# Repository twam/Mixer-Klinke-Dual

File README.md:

Mixer-Klinke-Dual
===

This repository is part of the USB audio mixer project described on https://www.twam.info/general/building-a-custom-usb-audio-mixer.

## License

[![CC BY-SA 4.0][cc-by-sa-shield]][cc-by-sa]

This work is licensed under a [Creative Commons Attribution-NonCommercial-ShareAlike 4.0 International License][cc-by-sa].

[![CC BY-SA 4.0][cc-by-sa-image]][cc-by-sa]

[cc-by-sa]: http://creativecommons.org/licenses/by-nc-sa/4.0/
[cc-by-sa-image]: https://licensebuttons.net/l/by-nc-sa/4.0/88x31.png
[cc-by-sa-shield]: https://img.shields.io/badge/License-CC%20BY--NC--SA%204.0-lightgrey.svg

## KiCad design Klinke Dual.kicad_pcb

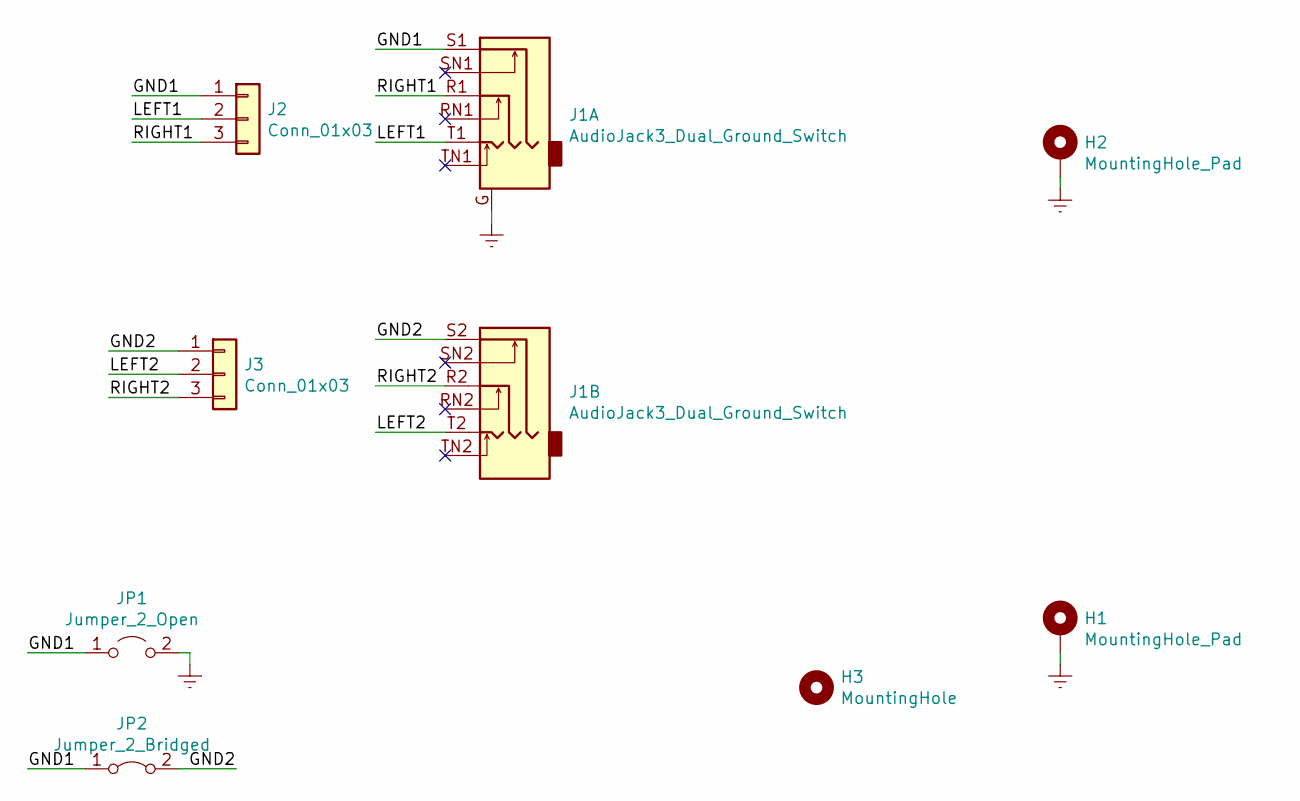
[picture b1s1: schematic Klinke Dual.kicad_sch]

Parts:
H1, H2: MountingHole_Pad; MountingHole_3.2mm_M3_DIN965_Pad
H3: MountingHole; MountingHole_3.2mm_M3_DIN965
J1: AudioJack3_Dual_Ground_Switch; Jack_6.35mm_Neutrik_NSJ12HF-1_Horizontal
J2, J3: Conn_01x03; PinHeader_1x03_P2.54mm_Vertical
JP1: Jumper_2_Open; SolderJumper-2_P1.3mm_Open_RoundedPad1.0x1.5mm
JP2: Jumper_2_Bridged; SolderJumper-2_P1.3mm_Open_RoundedPad1.0x1.5mm

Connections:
/GND1: J1.S1, J2.1, JP1.1 (A), JP2.1 (A)
/GND2: J1.S2, J3.1, JP2.2 (B)
/LEFT1: J1.T1, J2.2
/LEFT2: J1.T2, J3.2
/RIGHT1: J1.R1, J2.3
/RIGHT2: J1.R2, J3.3
Earth: H1.1, H2.1, J1.G, JP1.2 (B)

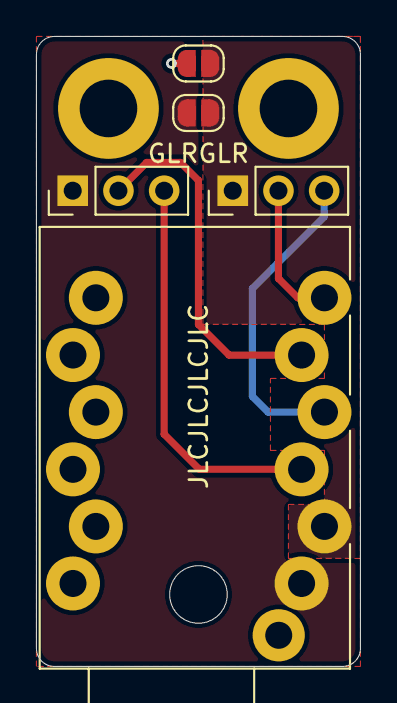
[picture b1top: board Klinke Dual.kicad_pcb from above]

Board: 2 copper layers, 18.0 x 35.0 mm, 8 parts (0 on the bottom side), 7 nets.

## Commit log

2021-03-13 Initial commit, Rev. 1
2022-01-07 Update to latest files
2022-01-07 Update to KiCad 6
2022-01-15 Add README
